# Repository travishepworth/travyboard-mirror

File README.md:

<h1 align="center">
travyboard
</h1>

## A corne style keyboard with the Pico SDK and TinyUSB

A personal project demonstrating how to build a keyboard using the
Raspberry Pi Pico microcontroller in c++. Intent on expanding to create more powerful
keyboards with more features (wireless coming soon).

### Photos
<div style="display: flex; justify-content: space-around;">

</div>

### Features

- 3d printed case
- 3x6 matrix with 3 button thumb clusters and 2 mode keys
- Split one way communication
- Full keymap controlled by the master pico
- Dynamic layers
- ws2812 rgb leds on every key

### Requirements for building

- Two Raspberry Pi Picos. I have the waveshare zeroes on the actual PCB.
- Cmake and gcc/g++ installed. May want to set up wsl2 on Windows.

### Setup

1. Clone this repository:

```sh
git clone https://github.com/travmonkey/travyboard.git
cd travyboard
```

2. Update the submodules:

```sh
# Includes the pico-sdk and rf modules
git submodule update --init --recursive
```

3. To build the project you need gcc-arm-none-eabi, cmake, and make installed:

```sh
cd firmware
mkdir build && cd build
cmake -DCMAKE_EXPORT_COMPILE_COMMANDS=ON ..
make
```

5. Mount and flash both picos with the master and slave compiled .uf2 code.
```sh
mkdir ~/rpi-pico
sudo fdisk -l # Find the pico device
sudo mount /dev/sdx1 /home/`<user>`/rpi-pico
sudo cp src/devices/right_half/right_half.uf2 /home/`<user>`/rpi-pico/
sudo cp src/devices/left_half/left_half.uf2 /home/`<user>`/rpi-pico/
```

Alternativly you can modify the script I wrote to include your own directories and username

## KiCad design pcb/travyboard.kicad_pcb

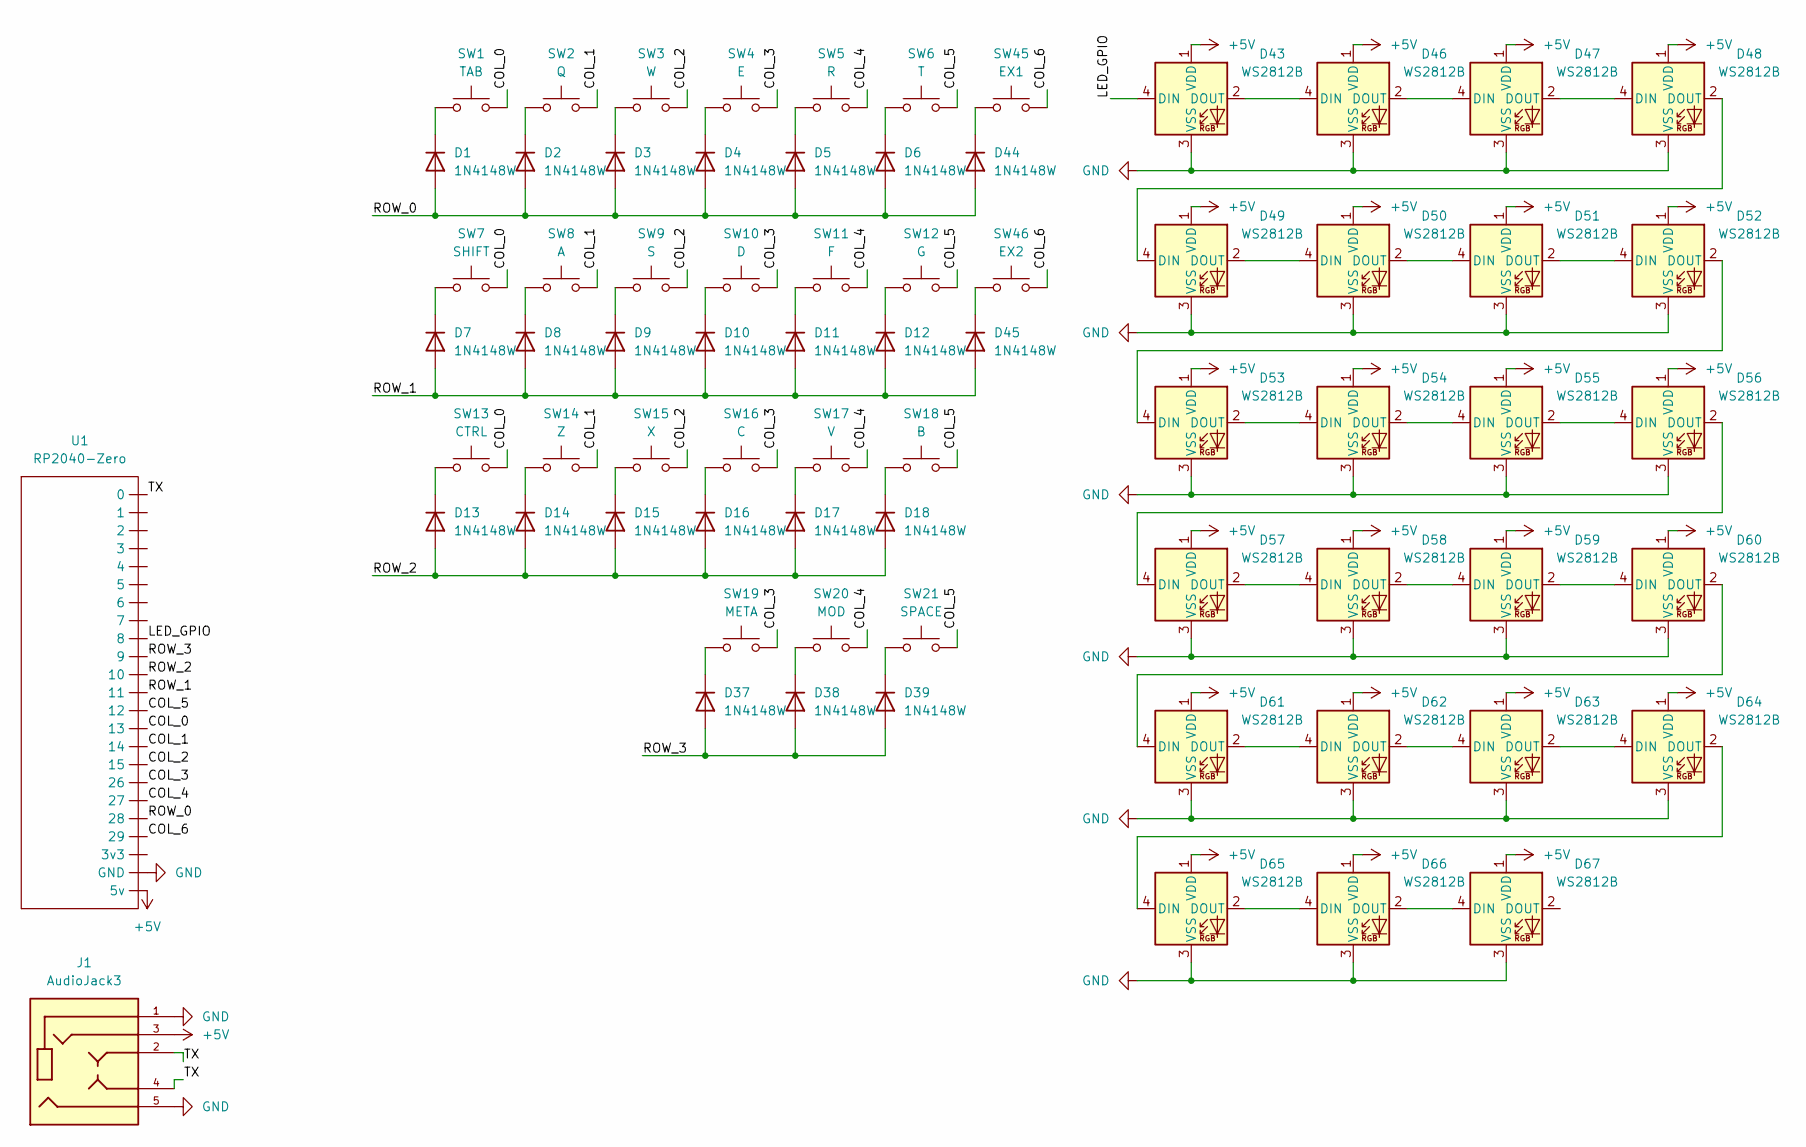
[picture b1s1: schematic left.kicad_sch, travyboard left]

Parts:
D1, D2, D3, D4, D5, D6, D7, D8, D9, D10, D11, D12, D13, D14, D15, D16, D17, D18, D37, D38, D39, D44, D45: 1N4148W; D_SOD-123
D43, D46, D47, D48, D49, D50, D51, D52, D53, D54, D55, D56, D57, D58, D59, D60, D61, D62, D63, D64, D65, D66, D67: WS2812B; LED_WS2812B_PLCC4_5.0x5.0mm_P3.2mm
J1: AudioJack3; CUI_SJ-3501-SMT-TR; PARTREV 1.05
SW1: TAB; CherryMX_Hotswap
SW2: Q; CherryMX_Hotswap
SW3: W; CherryMX_Hotswap
SW4: E; CherryMX_Hotswap
SW5: R; CherryMX_Hotswap
SW6: T; CherryMX_Hotswap
SW7: SHIFT; CherryMX_Hotswap
SW8: A; CherryMX_Hotswap
SW9: S; CherryMX_Hotswap
SW10: D; CherryMX_Hotswap
SW11: F; CherryMX_Hotswap
SW12: G; CherryMX_Hotswap
SW13: CTRL; CherryMX_Hotswap
SW14: Z; CherryMX_Hotswap
SW15: X; CherryMX_Hotswap
SW16: C; CherryMX_Hotswap
SW17: V; CherryMX_Hotswap
SW18: B; CherryMX_Hotswap
SW19: META; CherryMX_Hotswap
SW20: MOD; CherryMX_Hotswap
SW21: SPACE; CherryMX_Hotswap
SW45: EX1; CherryMX_Hotswap
SW46: EX2; CherryMX_Hotswap
U1: RP2040-Zero

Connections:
+5V: D43.1 (VDD), D46.1 (VDD), D47.1 (VDD), D48.1 (VDD), D49.1 (VDD), D50.1 (VDD), D51.1 (VDD), D52.1 (VDD), D53.1 (VDD), D54.1 (VDD), D55.1 (VDD), D56.1 (VDD), D57.1 (VDD), D58.1 (VDD), D59.1 (VDD), D60.1 (VDD), D61.1 (VDD), D62.1 (VDD), D63.1 (VDD), D64.1 (VDD), D65.1 (VDD), D66.1 (VDD), D67.1 (VDD), J1.3, U1.5v; also elsewhere on the board
/Left Half/COL_0: SW1.2, SW7.2, SW13.2, U1.13
/Left Half/COL_1: SW2.2, SW8.2, SW14.2, U1.14
/Left Half/COL_2: SW3.2, SW9.2, SW15.2, U1.15
/Left Half/COL_3: SW4.2, SW10.2, SW16.2, SW19.2, U1.26
/Left Half/COL_4: SW5.2, SW11.2, SW17.2, SW20.2, U1.27
/Left Half/COL_5: SW6.2, SW12.2, SW18.2, SW21.2, U1.12
/Left Half/COL_6: SW45.2, SW46.2, U1.29
/Left Half/LED_GPIO: D43.4 (DIN), U1.8
/Left Half/ROW_0: D1.2 (A), D2.2 (A), D3.2 (A), D4.2 (A), D5.2 (A), D6.2 (A), D44.2 (A), U1.28
/Left Half/ROW_1: D7.2 (A), D8.2 (A), D9.2 (A), D10.2 (A), D11.2 (A), D12.2 (A), D45.2 (A), U1.11
/Left Half/ROW_2: D13.2 (A), D14.2 (A), D15.2 (A), D16.2 (A), D17.2 (A), D18.2 (A), U1.10
/Left Half/ROW_3: D37.2 (A), D38.2 (A), D39.2 (A), U1.9
/Left Half/TX: J1.2, J1.4, U1.0
GND: D43.3 (VSS), D46.3 (VSS), D47.3 (VSS), D48.3 (VSS), D49.3 (VSS), D50.3 (VSS), D51.3 (VSS), D52.3 (VSS), D53.3 (VSS), D54.3 (VSS), D55.3 (VSS), D56.3 (VSS), D57.3 (VSS), D58.3 (VSS), D59.3 (VSS), D60.3 (VSS), D61.3 (VSS), D62.3 (VSS), D63.3 (VSS), D64.3 (VSS), D65.3 (VSS), D66.3 (VSS), D67.3 (VSS), J1.1, J1.5, U1.GND; also elsewhere on the board
unnamed: D1.1 (K), SW1.1
unnamed: D2.1 (K), SW2.1
unnamed: D3.1 (K), SW3.1
unnamed: D4.1 (K), SW4.1
unnamed: D5.1 (K), SW5.1
unnamed: D6.1 (K), SW6.1
unnamed: D7.1 (K), SW7.1
unnamed: D8.1 (K), SW8.1
unnamed: D9.1 (K), SW9.1
unnamed: D10.1 (K), SW10.1
unnamed: D11.1 (K), SW11.1
unnamed: D12.1 (K), SW12.1
unnamed: D13.1 (K), SW13.1
unnamed: D14.1 (K), SW14.1
unnamed: D15.1 (K), SW15.1
unnamed: D16.1 (K), SW16.1
unnamed: D17.1 (K), SW17.1
unnamed: D18.1 (K), SW18.1
unnamed: D37.1 (K), SW19.1
unnamed: D38.1 (K), SW20.1
unnamed: D39.1 (K), SW21.1
unnamed: D43.2 (DOUT), D46.4 (DIN)
unnamed: D44.1 (K), SW45.1
unnamed: D45.1 (K), SW46.1
unnamed: D46.2 (DOUT), D47.4 (DIN)
unnamed: D47.2 (DOUT), D48.4 (DIN)
unnamed: D48.2 (DOUT), D49.4 (DIN)
unnamed: D49.2 (DOUT), D50.4 (DIN)
unnamed: D50.2 (DOUT), D51.4 (DIN)
unnamed: D51.2 (DOUT), D52.4 (DIN)
unnamed: D52.2 (DOUT), D53.4 (DIN)
unnamed: D53.2 (DOUT), D54.4 (DIN)
unnamed: D54.2 (DOUT), D55.4 (DIN)
unnamed: D55.2 (DOUT), D56.4 (DIN)
unnamed: D56.2 (DOUT), D57.4 (DIN)
unnamed: D57.2 (DOUT), D58.4 (DIN)
unnamed: D58.2 (DOUT), D59.4 (DIN)
unnamed: D59.2 (DOUT), D60.4 (DIN)
unnamed: D60.2 (DOUT), D61.4 (DIN)
unnamed: D61.2 (DOUT), D62.4 (DIN)
unnamed: D62.2 (DOUT), D63.4 (DIN)
unnamed: D63.2 (DOUT), D64.4 (DIN)
unnamed: D64.2 (DOUT), D65.4 (DIN)
unnamed: D65.2 (DOUT), D66.4 (DIN)
unnamed: D66.2 (DOUT), D67.4 (DIN)

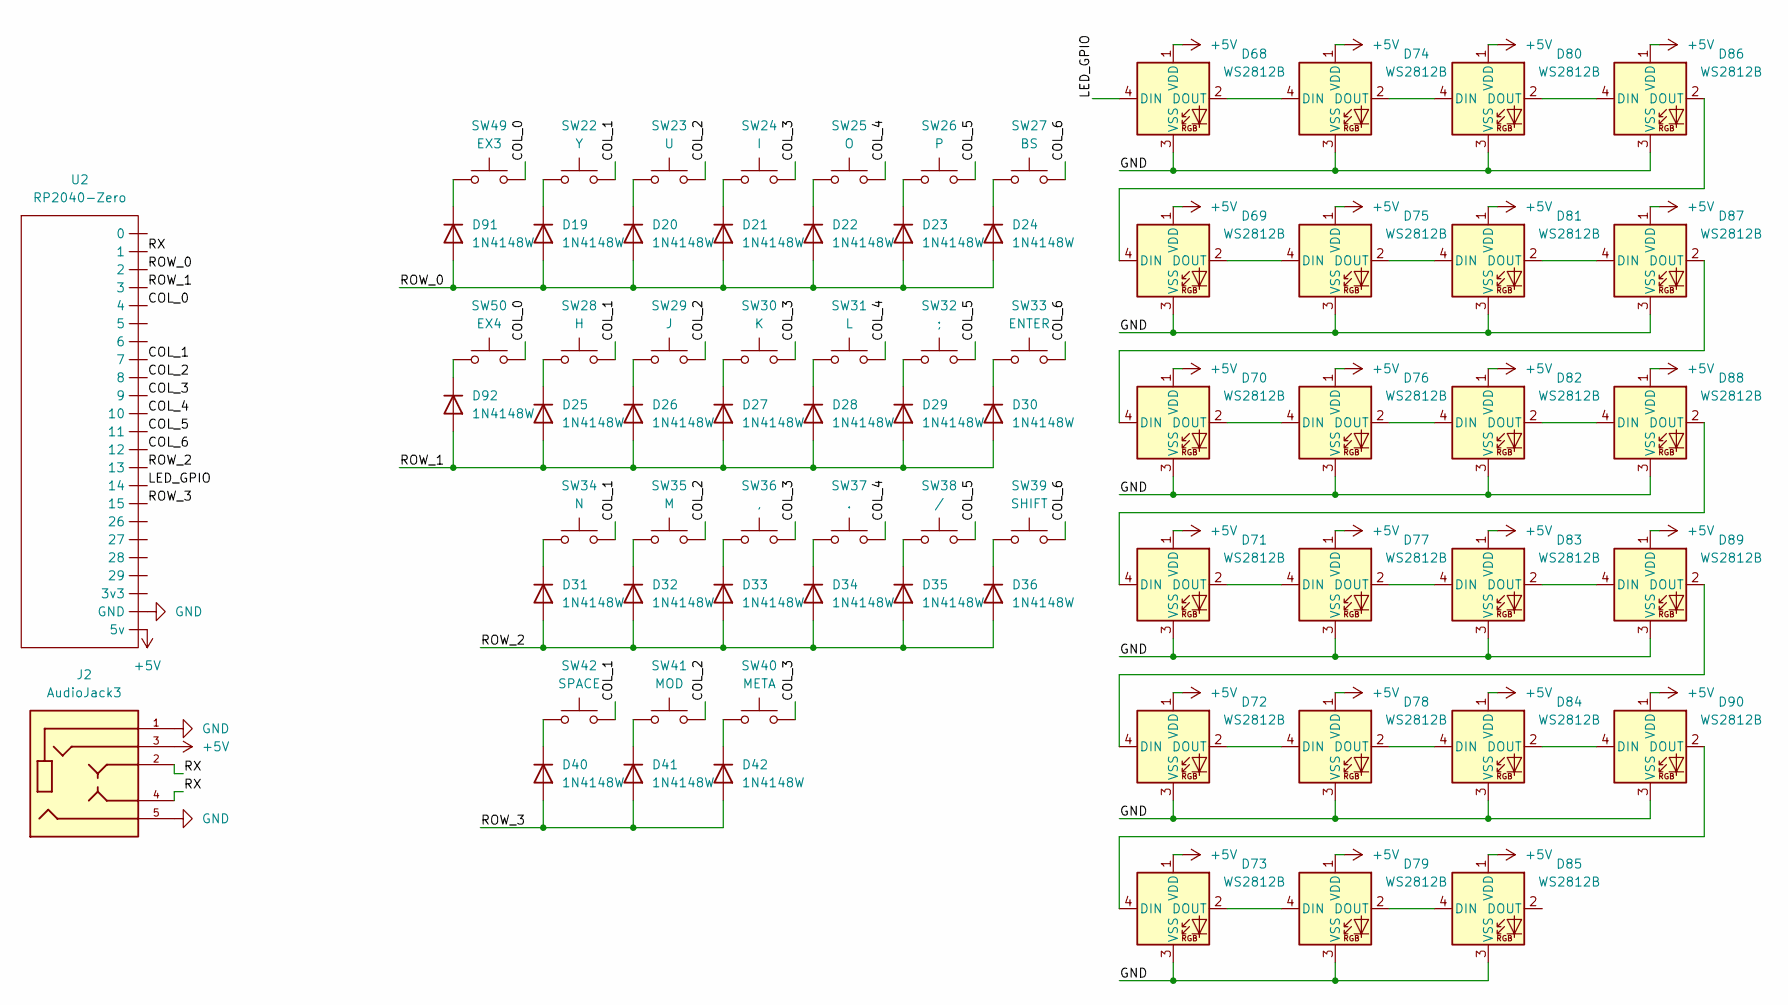
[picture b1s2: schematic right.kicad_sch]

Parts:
D19, D20, D21, D22, D23, D24, D25, D26, D27, D28, D29, D30, D31, D32, D33, D34, D35, D36, D40, D41, D42, D91, D92: 1N4148W; D_SOD-123
D68, D69, D70, D71, D72, D73, D74, D75, D76, D77, D78, D79, D80, D81, D82, D83, D84, D85, D86, D87, D88, D89, D90: WS2812B; LED_WS2812B_PLCC4_5.0x5.0mm_P3.2mm
J2: AudioJack3; CUI_SJ-3501-SMT-TR; PARTREV 1.05
SW22: Y; CherryMX_Hotswap
SW23: U; CherryMX_Hotswap
SW24: I; CherryMX_Hotswap
SW25: O; CherryMX_Hotswap
SW26: P; CherryMX_Hotswap
SW27: BS; CherryMX_Hotswap
SW28: H; CherryMX_Hotswap
SW29: J; CherryMX_Hotswap
SW30: K; CherryMX_Hotswap
SW31: L; CherryMX_Hotswap
SW32: ;; CherryMX_Hotswap
SW33: ENTER; CherryMX_Hotswap
SW34: N; CherryMX_Hotswap
SW35: M; CherryMX_Hotswap
SW36: ,; CherryMX_Hotswap
SW37: .; CherryMX_Hotswap
SW38: /; CherryMX_Hotswap
SW39: SHIFT; CherryMX_Hotswap
SW40: META; CherryMX_Hotswap
SW41: MOD; CherryMX_Hotswap
SW42: SPACE; CherryMX_Hotswap
SW49: EX3; CherryMX_Hotswap
SW50: EX4; CherryMX_Hotswap
U2: RP2040-Zero

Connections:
+5V: D68.1 (VDD), D69.1 (VDD), D70.1 (VDD), D71.1 (VDD), D72.1 (VDD), D73.1 (VDD), D74.1 (VDD), D75.1 (VDD), D76.1 (VDD), D77.1 (VDD), D78.1 (VDD), D79.1 (VDD), D80.1 (VDD), D81.1 (VDD), D82.1 (VDD), D83.1 (VDD), D84.1 (VDD), D85.1 (VDD), D86.1 (VDD), D87.1 (VDD), D88.1 (VDD), D89.1 (VDD), D90.1 (VDD), J2.3, U2.5v; also elsewhere on the board
/Right Half/COL_0: SW49.2, SW50.2, U2.4
/Right Half/COL_1: SW22.2, SW28.2, SW34.2, SW42.2, U2.7
/Right Half/COL_2: SW23.2, SW29.2, SW35.2, SW41.2, U2.8
/Right Half/COL_3: SW24.2, SW30.2, SW36.2, SW40.2, U2.9
/Right Half/COL_4: SW25.2, SW31.2, SW37.2, U2.10
/Right Half/COL_5: SW26.2, SW32.2, SW38.2, U2.11
/Right Half/COL_6: SW27.2, SW33.2, SW39.2, U2.12
/Right Half/LED_GPIO: D68.4 (DIN), U2.14
/Right Half/ROW_0: D19.2 (A), D20.2 (A), D21.2 (A), D22.2 (A), D23.2 (A), D24.2 (A), D91.2 (A), U2.2
/Right Half/ROW_1: D25.2 (A), D26.2 (A), D27.2 (A), D28.2 (A), D29.2 (A), D30.2 (A), D92.2 (A), U2.3
/Right Half/ROW_2: D31.2 (A), D32.2 (A), D33.2 (A), D34.2 (A), D35.2 (A), D36.2 (A), U2.13
/Right Half/ROW_3: D40.2 (A), D41.2 (A), D42.2 (A), U2.15
/Right Half/RX: J2.2, J2.4, U2.1
GND: D68.3 (VSS), D69.3 (VSS), D70.3 (VSS), D71.3 (VSS), D72.3 (VSS), D73.3 (VSS), D74.3 (VSS), D75.3 (VSS), D76.3 (VSS), D77.3 (VSS), D78.3 (VSS), D79.3 (VSS), D80.3 (VSS), D81.3 (VSS), D82.3 (VSS), D83.3 (VSS), D84.3 (VSS), D85.3 (VSS), D86.3 (VSS), D87.3 (VSS), D88.3 (VSS), D89.3 (VSS), D90.3 (VSS), J2.1, J2.5, U2.GND; also elsewhere on the board
unnamed: D19.1 (K), SW22.1
unnamed: D20.1 (K), SW23.1
unnamed: D21.1 (K), SW24.1
unnamed: D22.1 (K), SW25.1
unnamed: D23.1 (K), SW26.1
unnamed: D24.1 (K), SW27.1
unnamed: D25.1 (K), SW28.1
unnamed: D26.1 (K), SW29.1
unnamed: D27.1 (K), SW30.1
unnamed: D28.1 (K), SW31.1
unnamed: D29.1 (K), SW32.1
unnamed: D30.1 (K), SW33.1
unnamed: D31.1 (K), SW34.1
unnamed: D32.1 (K), SW35.1
unnamed: D33.1 (K), SW36.1
unnamed: D34.1 (K), SW37.1
unnamed: D35.1 (K), SW38.1
unnamed: D36.1 (K), SW39.1
unnamed: D40.1 (K), SW42.1
unnamed: D41.1 (K), SW41.1
unnamed: D42.1 (K), SW40.1
unnamed: D68.2 (DOUT), D74.4 (DIN)
unnamed: D69.4 (DIN), D86.2 (DOUT)
unnamed: D69.2 (DOUT), D75.4 (DIN)
unnamed: D70.4 (DIN), D87.2 (DOUT)
unnamed: D70.2 (DOUT), D76.4 (DIN)
unnamed: D71.4 (DIN), D88.2 (DOUT)
unnamed: D71.2 (DOUT), D77.4 (DIN)
unnamed: D72.4 (DIN), D89.2 (DOUT)
unnamed: D72.2 (DOUT), D78.4 (DIN)
unnamed: D73.4 (DIN), D90.2 (DOUT)
unnamed: D73.2 (DOUT), D79.4 (DIN)
unnamed: D74.2 (DOUT), D80.4 (DIN)
unnamed: D75.2 (DOUT), D81.4 (DIN)
unnamed: D76.2 (DOUT), D82.4 (DIN)
unnamed: D77.2 (DOUT), D83.4 (DIN)
unnamed: D78.2 (DOUT), D84.4 (DIN)
unnamed: D79.2 (DOUT), D85.4 (DIN)
unnamed: D80.2 (DOUT), D86.4 (DIN)
unnamed: D81.2 (DOUT), D87.4 (DIN)
unnamed: D82.2 (DOUT), D88.4 (DIN)
unnamed: D83.2 (DOUT), D89.4 (DIN)
unnamed: D84.2 (DOUT), D90.4 (DIN)
unnamed: D91.1 (K), SW49.1
unnamed: D92.1 (K), SW50.1

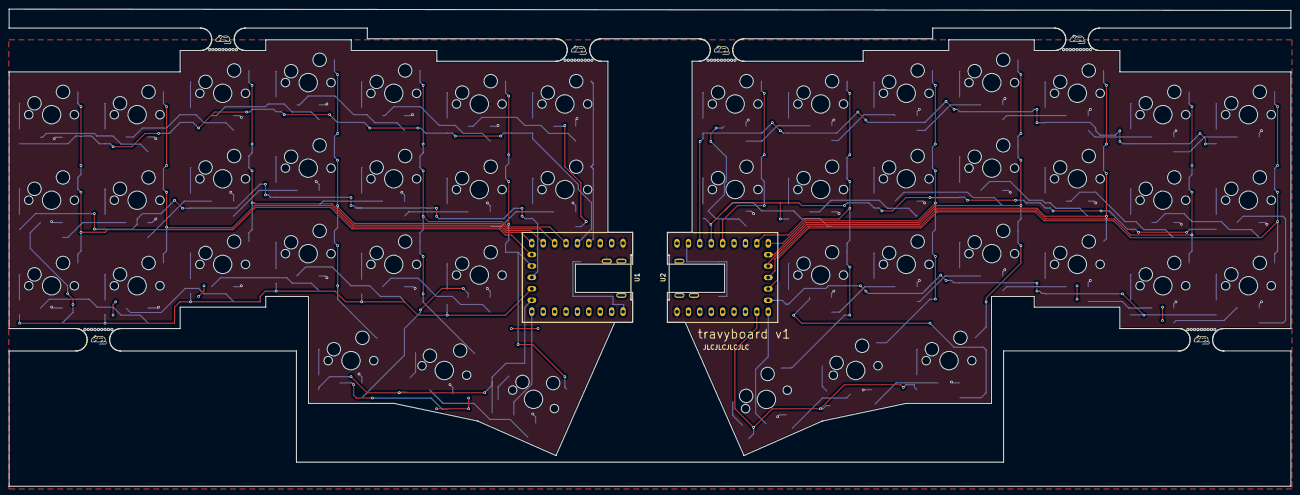
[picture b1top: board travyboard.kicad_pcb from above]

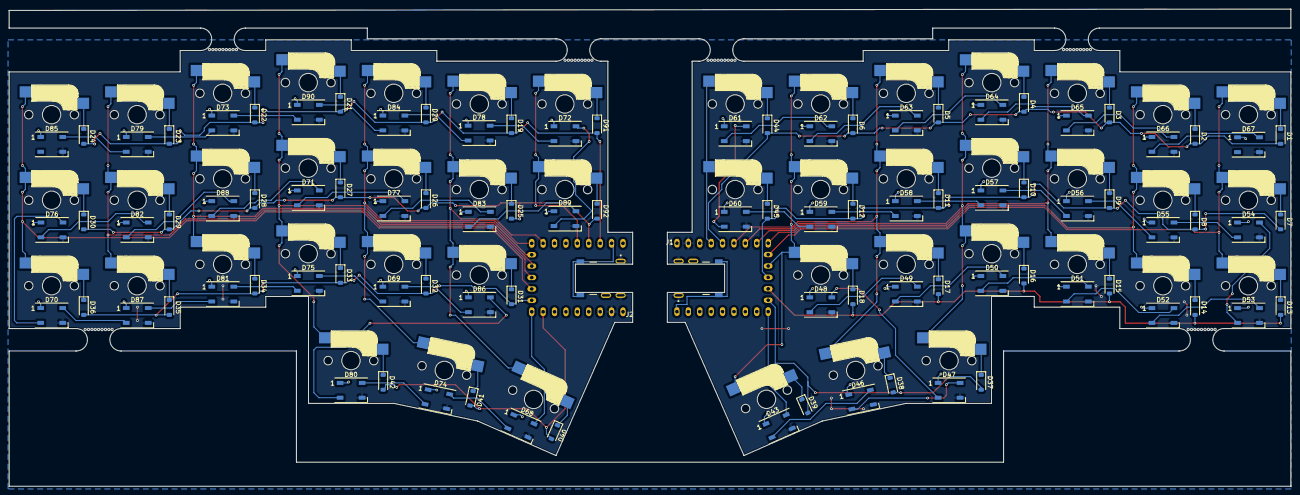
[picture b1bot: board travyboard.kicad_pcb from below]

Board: 2 copper layers, 285.5 x 106.3 mm, 148 parts (94 on the bottom side), 118 nets.

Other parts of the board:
mouse-bite-5mm-10mm, mouse-bite-5mm-10mm#2, mouse-bite-5mm-10mm#3, mouse-bite-5mm-10mm#4, mouse-bite-5mm-10mm#5, mouse-bite-5mm-10mm#6: VAL**; mouse-bite-5mm-10mm

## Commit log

2025-03-17 Rework edgecuts and change to waveshare rp2040 zero
2025-04-01 Firmware updates
2025-04-01 Finalize pcb for printing
2025-04-01 Implement smarter layer switching
2025-04-01 Update keymap
2025-04-01 Add stls for the keyboard case
2025-04-02 Update flash script
2025-04-02 Readme updates
2025-04-03 Remove kicad backups from git
2025-04-21 Improve comments
2025-05-09 Remove stale submodule
2025-05-10 Init development of firmware-v2
2025-05-12 Start early development
2025-05-12 Ignore notes
2025-05-20 Barebones logic implemented
2025-05-20 Initialize proper keymap and layer handling
2025-05-23 Re-write keymap and layer handling
2025-05-23 Optimize board reading
2025-05-23 Typo
2025-05-23 Move to keymap defined globals
2025-05-23 Type changes
2025-05-23 Remove temporary build
2025-05-23 Add right_half output
2025-05-23 Add extra subdir
2025-05-24 Initialize debouncing
2025-05-24 Init right only keymap
2025-05-24 Init right only
2025-05-30 Update submodule
2025-05-30 Move usb_descriptors
2025-05-30 Fix state read bug
2025-05-30 Fix layer indexing logic
2025-05-30 Move main structs to data
2025-05-30 Create single-halved keymap
2025-05-30 Simplify keymap copy logic
2025-05-30 Add subdir keymap_files
2025-05-30 Prepare CMake for single half keyboard
2025-05-30 Init uart files
2025-05-30 Fix: convert mouse-bite.pretty from submodule to local folder
2025-06-01 Initialize split usage
2025-06-03 Claude go crazy | will re-implement later
2025-06-05 Initialize left half
2025-06-05 Improve flashing script
2025-06-05 Make keymaps readable
2025-06-05 Improve matrix logic
2025-06-05 Rework debounce logic
2025-06-05 Implement full keyboard logic
2025-06-05 Move main logic to right half
2025-06-05 Add left half
2025-06-05 Fix return layer
2025-06-05 Add subdirectory
2025-06-07 More structured uart packet
2025-06-07 Entire layer processing re-work
2025-06-07 Incorrect codes assigned
2025-06-07 Add more utility definitions to enum
2025-06-07 Optimize flow
2025-06-07 Format
2025-06-07 Increase debounce time
2025-06-07 Add matrix functions
2025-06-08 Better comments
2025-06-08 Fix major bug in locked keycodes
2025-06-08 Clean up comments
2025-06-08 Fully functional keyboard
2025-06-08 Remove un-needed field
2025-06-08 Fix UART recieve and transmit
2025-06-08 Remove unnecessary CMakeLists.txt
2025-06-08 Update flash script to user instead of sudo
2025-06-08 Remove old firmware directory
2025-06-08 Remove-submodules old path
2025-06-08 Add new submodule path
2025-06-08 Remove old gitignore paths
2025-06-08 Move to firmware directory
2025-06-08 Fix typo
2025-06-08 Update readme for new firmware
2025-06-08 Move usb function to tusb.c
2025-06-08 Fix sudo handing
2025-06-08 Initialize build workflow
2025-06-08 Remove picotool dependency
2025-06-08 Update workflow
2025-06-08 Simplify workflow
2025-06-08 Remove temp todo - check issues
2025-06-09 Move to rf24
2025-06-09 Remove old CMakeLists
2025-06-09 Re-organize keymap definitions
2025-06-16 More effecient matrix scanning
2025-06-16 Disable workflow
2025-06-22 Re-enable workflow
2025-06-22 Test forgejo runner
2025-06-22 Move .github -> .forgejo
2025-06-22 Use apk instead of apt-get
2025-06-22 Update paths and remove sudo
2025-06-22 Use apk add
